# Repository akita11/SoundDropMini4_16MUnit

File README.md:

# SoundDropMini4MUnit

音声再生IC CH7003を使用した音声再生モジュールです。4MB（または16MB）のフラッシュメモリを搭載しており、PCにUSB Type-Cケーブルで接続するとUSBメモリとして認識され、そこにMP3音声データ等をコピーします。その音声データをGrove端子のシリアル(UART)通信で再生制御できます。UIFlow(v1)用のブロックもあります。

※CH7003に関する情報は[メーカWebページ](https://www.ch2003.com/h-col-124.html)等で検索してください。要点は以下にまとめてあります。

## 使い方（接続方法）

以下のようにスピーカやアンプを接続し、Grove端子からの制御で音声を再生します。必要に応じて基板裏面の半田ジャンパをショート・カットしてください。

### アンプ付きスピーカに接続する場合

3.5mmジャック（ステレオ：上部中央）に3.5mmステレオケーブル等でアンプに接続します。
またJP1を半田等でショートしますにします。

### スピーカを直接接続する場合

基板上部にある1.25mmピッチコネクタ(Molex 53047-0210用)をとりつける端子があり、市販の小型スピーカ（M5Stack本体に使われているものなど。AliExpressやTaobaoでも同等品があります）を接続することができます。※隙間がせまく差し込みにくいので注意してください。
またJP1を開放（初期状態）します。

### 3.5mmジャックに直接スピーカを接続する方法

3.5mmジャックに直接スピーカを接続することもできます。その場合は、基板裏面のハンダジャンパを以下のように修正してください。（スピーカはモノラル再生となります）
※結線は、プラグの根本側から、GND-SPK-NC(無接続)、の順となります。そのため、ステレオ型スピーカではL側からの再生になります。またモノラルプラグでは、このGNDとSPKが短絡されるため使用できません。

- JP2をカット
- JP3・JP4の中央と△マーク側をカットし、中央と反対側（△マークがない側）をショート

## 本体機能の設定

[メーカWebページ](https://www.ch2003.com/h-col-124.html)から"CH7003语音芯片模块.zip"）をダウンロードし、その中にあるテスト用ソフトウエア（Windows用）で、音量などを設定できます。ただし日本語PCでは文字化けするため、データシート中のソフトウエア画面と比べながら使うことになります。なお後述のコマンドでも設定できます。

## 使い方（ソフトウエア）

あらかじめ、本体基板の一部にあるUSB Type-CにUSB Type-Cケーブルを使ってPCへ接続し、現れるドライブに使用する音声データ（*.mp3）をコピーしておきます。なおファイル名は、「"001"から"999"の3桁の数値」のみが有効（CH7003の仕様）となり、その数値が「曲番号」となります。
※mp3のビットレートが高すぎると、正しく再生されない場合があるようです。その場合はビットレートを落として使ってください。

### UIFlow(v1)での使い方

[SoundDropMiniUNIT](https://github.com/akita11/SoundDropMIniUNIT)のページから「SoundDropMini.m5b」をダウンロードし、UIFlow(v1)の"Custom"の"Open *.m5b"からこのファイルを指定すると、Init、Play、Stopの3つのブロックを使用できます。（SoundDropMiniUNITと主な再生関連のコマンドは同一です）

- SoundDropMini_Init : 初期化。最初に1回だけ使用します。"TX"と"RX"には、使用するGroveポート・マイコン本体にあわせて、使用するピン番号を指定します。例えば、M5StackBasicのPortA（本体の赤いコネクタ）の場合は、上図のようにTX=21、RX=22を指定します。M5StackCore2のPortAの場合は、TX=32、RX=33となります。
- SoundDropMini_Play : numに指定した「曲番号」の音声を再生します。
- SoundDropMini_Stop : 再生中の音声を停止します。

※この例では再生した直後に停止していますので、音声がほぼ聞こえません。実際には目的に合わせて使い分けてください。

### その他のソフトウエアでの使い方

搭載されている音声再生IC(CH7003)のデータシート等を参考に、制御コマンドをUART経由で送信して使用してください。通信プロトコルは「9600bps/N81」です。
制御コマンドの一部を以下にまとめます。

- 次の曲の再生: 0x7e 0x11 0x00 0x02 0x00 0x00 0xef
- 前の曲の再生: 0x7e 0x12 0x00 0x02 0x00 0x00 0xef
- 指定した曲(HH:LL＝曲番号(上位/下位の順))の再生: 0x7e 0x13 0x00 0x02 HH LL 0xef
- 音量UP: 7e 0x14 0x00 0x02 0x00 0x00 0xef
- 音量DOWN: 0x7e 0x15 0x00 0x02 0x00 0x00 0xef
- 音量をNNに設定: 0x7e 0x16 0x00 0x02 0x00 NN 0xef
- 再生停止: 0x7e 0x26 0x00 0x02 0x00 0x00 0xef

## Author

Junichi Akita (@akita11) / akita@ifdl.jp

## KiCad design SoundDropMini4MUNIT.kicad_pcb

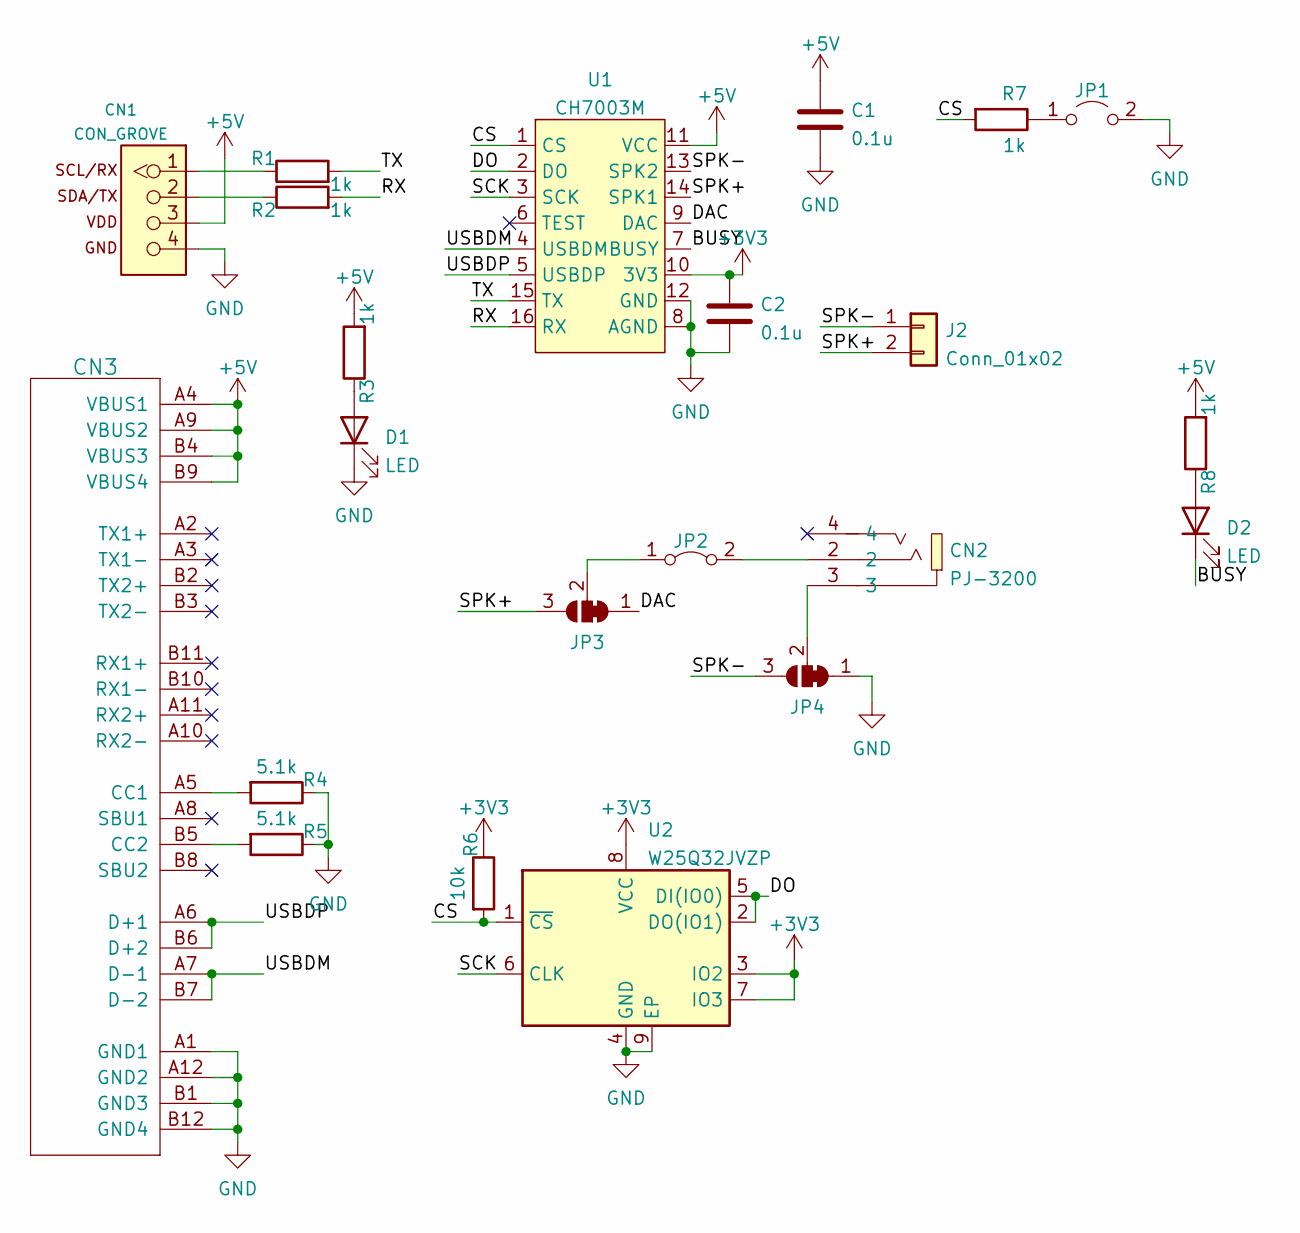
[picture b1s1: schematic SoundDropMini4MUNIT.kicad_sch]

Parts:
C1, C2: 0.1u; C_0603_1608Metric
CN1: CON_GROVE; CON_GROVE_H
CN2: PJ-3200; AUDIO-TH_PJ-3200; LCSC Part C2689690
CN3: CON_USB-CPCBPLUG; USB-C_PCBPLUG
D1, D2: LED; LED_0603_1608Metric
J2: Conn_01x02; Molex_PicoBlade_53047-0210_1x02_P1.25mm_Vertical
JP1: Jumper_2_Open; SolderJumper-2_P1.3mm_Open_Pad1.0x1.5mm
JP2: Jumper_2_Bridged; SolderJumper-2_P1.3mm_Bridged_Pad1.0x1.5mm
JP3, JP4: SolderJumper_3_Bridged12; SolderJumper-3_P1.3mm_Bridged12_Pad1.0x1.5mm
R1, R2, R3, R7, R8: 1k; R_0603_1608Metric
R4, R5: 5.1k; R_0603_1608Metric
R6: 10k; R_0603_1608Metric
U1: CH7003M; SOP-16_4.4x10.4mm_P1.27mm
U2: W25Q32JVZP; WSON-8-1EP_6x5mm_P1.27mm_EP3.4x4.3mm

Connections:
+3V3: C2.1, R6.1, U1.10 (3V3), U2.3 (IO2), U2.7 (IO3), U2.8 (VCC)
+5V: C1.1, CN1.3, CN3.A4 (VBUS1), CN3.A9 (VBUS2), CN3.B4 (VBUS3), CN3.B9 (VBUS4), R3.2, R8.2, U1.11 (VCC)
/BUSY: D2.1 (K), U1.7 (BUSY)
/CS: R6.2, R7.2, U1.1 (CS), U2.1 (~CS)
/DAC: JP3.1 (A), U1.9 (DAC)
/DO: U1.2 (DO), U2.2 (DO(IO1)), U2.5 (DI(IO0))
/RX: R2.2, U1.16 (RX)
/SCK: U1.3 (SCK), U2.6 (CLK)
/SPK+: J2.2, JP3.3 (B), U1.14 (SPK1)
/SPK-: J2.1, JP4.3 (B), U1.13 (SPK2)
/TX: R1.2, U1.15 (TX)
/USBDM: CN3.A7 (D-1), CN3.B7 (D-2), U1.4 (USBDM)
/USBDP: CN3.A6 (D+1), CN3.B6 (D+2), U1.5 (USBDP)
GND: C1.2, C2.2, CN1.4, CN3.A1 (GND1), CN3.A12 (GND2), CN3.B1 (GND3), CN3.B12 (GND4), D1.1 (K), JP1.2 (B), JP4.1 (A), R4.1, R5.1, U1.8 (AGND), U1.12 (GND), U2.4 (GND), U2.9 (EP)
unnamed: CN1.1, R1.1
unnamed: CN1.2, R2.1
unnamed: CN2.2, JP2.2 (B)
unnamed: CN2.3, JP4.2 (C)
unnamed: CN3.A5 (CC1), R4.2
unnamed: CN3.B5 (CC2), R5.2
unnamed: D1.2 (A), R3.1
unnamed: D2.2 (A), R8.1
unnamed: JP1.1 (A), R7.1
unnamed: JP2.1 (A), JP3.2 (C)

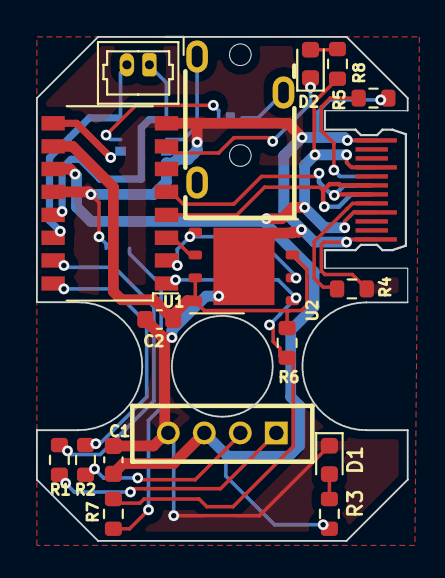
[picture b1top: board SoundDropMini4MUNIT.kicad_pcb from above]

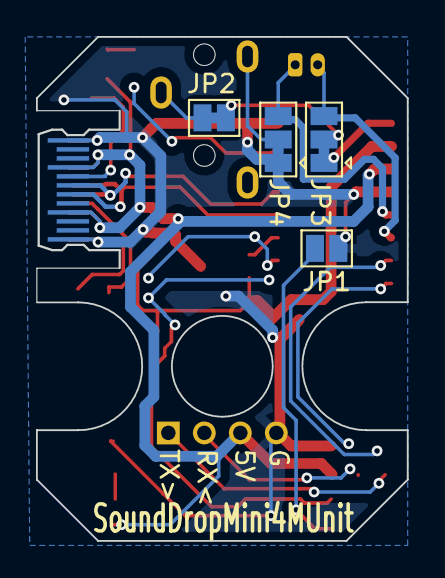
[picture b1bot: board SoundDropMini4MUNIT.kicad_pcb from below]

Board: 2 copper layers, 20.6 x 28.0 mm, 22 parts (4 on the bottom side), 24 nets.

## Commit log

2025-05-21 initial commit, no photo
2025-06-05 add pho
2025-06-05 add block photo
2025-06-05 photo name fix
2026-04-09 Update README with speaker connection instructions
    Added instructions for connecting speakers directly to the 3.5mm jack, including jumper modifications.
